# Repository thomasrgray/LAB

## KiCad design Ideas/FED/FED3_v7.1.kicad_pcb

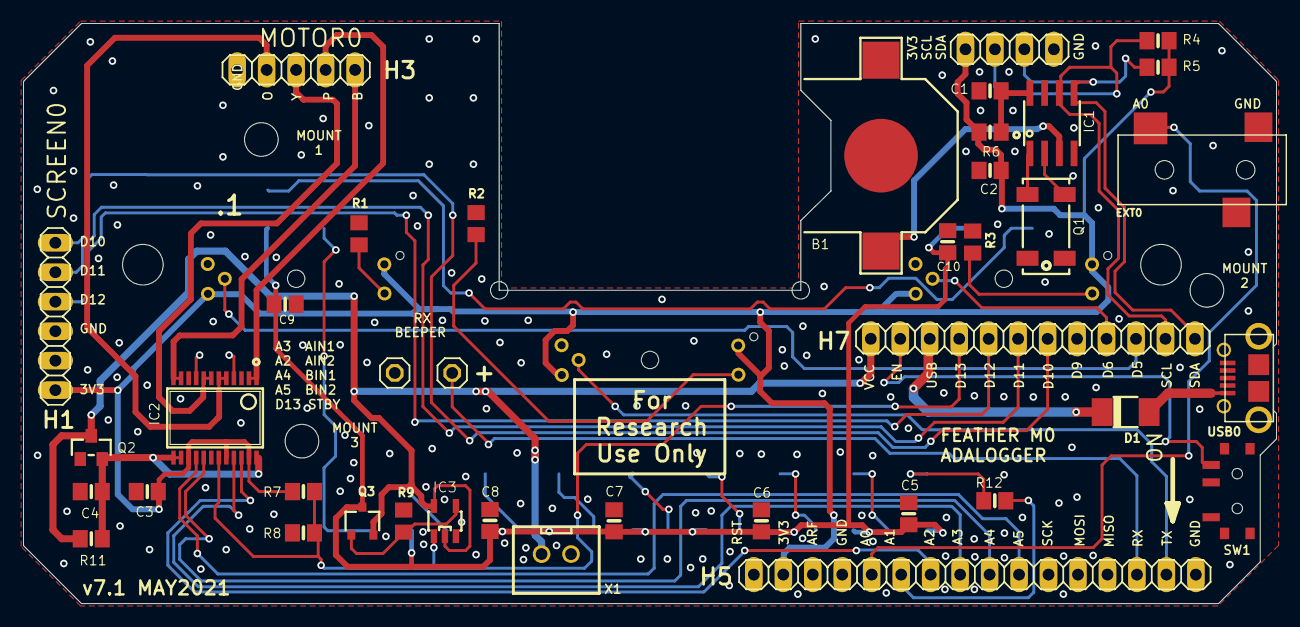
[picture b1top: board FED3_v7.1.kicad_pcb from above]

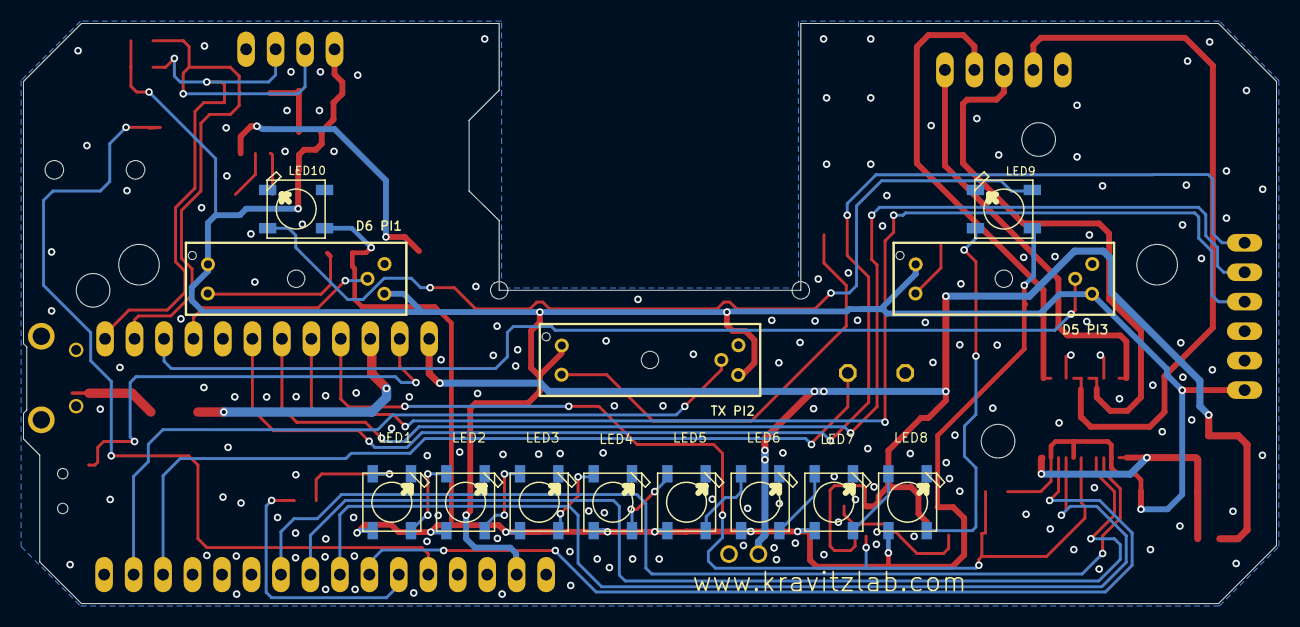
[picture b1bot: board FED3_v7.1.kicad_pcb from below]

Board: 2 copper layers, 108.0 x 50.0 mm, 60 parts (13 on the bottom side), 46 nets.

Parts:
@HOLE0, @HOLE1, @HOLE2, @HOLE3, @HOLE4, @HOLE5, @HOLE6: (no value)
AUX_I2C0: 1X04
B1: CR1220
BEEP1, BEEP2: 1X01
C1, C2, C5, C6, C7, C8, C9, C10: 10uF; 0805-NO
C3, C4: 10µF; 0805-NO
D1: DO-214AC
EXT0: 35RASMT2BHNTRX
FEATHER_L0: 1X16
FEATHER_R0: 1X12
IC1: RTC_PCF8523T; SOIC8_150MIL
IC2: TB6612 SSOP; SSOP24
IC3: M74VHC1GT50DTT1G; SOT23-5
LED1, LED2, LED3, LED4, LED5, LED6, LED7, LED8, LED9, LED10: WS2812B5050; WS2812B
MOTOR0: 1X05
PI1, PI2, PI3: GP1A57HR
Q1: 32.768; CRYSTAL_8X3.8
Q2: DMG3415; SOT23-WIDE
Q3: TSMT3
R1, R2, R3: 1k; R0805
R4, R5: 4K7; 0805-NO
R6: 1K; 0805-NO
R7: DNI; 0805-NO
R8: 4k7; 0805-NO
R9: 37k; R0805
R11: 0; 0805-NO
R12: 470; 0805-NO
SCREEN0: 1X06
SW1: SSSS811101
USB0: USB_MICRO_B; ZX62D-B-5P8
X1: B2B-PH-K-S(LF)(SN); JST-XH-02-PACKAGE-ROUND-PAD

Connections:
3V3: AUX_I2C0.1, C2.1, C3.1, FEATHER_L0.2, IC2.15, IC2.20, IC2.23, PI1.1, PI1.3, PI2.1, PI2.3, PI3.1, PI3.3, R4.1, R5.2, R6.1, R7.2, SCREEN0.6
A0: EXT0.4, FEATHER_L0.5
A1: FEATHER_L0.6, R12.2
A2: FEATHER_L0.7, IC2.22
A3: FEATHER_L0.8, IC2.21
A4: FEATHER_L0.9, IC2.17
A5: FEATHER_L0.10, IC2.16
BLUE: IC2.11, IC2.12, MOTOR0.5
D5: FEATHER_R0.10, PI3.4
D6: FEATHER_R0.9, PI1.4
D10: FEATHER_R0.7, SCREEN0.1
D11: FEATHER_R0.6, SCREEN0.2
D12: FEATHER_R0.5, SCREEN0.3
D13: FEATHER_R0.4, IC2.19, IC3.1, R7.1, R8.2
EN: FEATHER_R0.2, SW1.3
GND: AUX_I2C0.4, B1.-, BEEP2.1, C1.2, C2.2, C3.2, C4.2, C5.2, C6.2, C7.2, C8.2, C9.2, C10.2, EXT0.5, FEATHER_L0.4, FEATHER_L0.16, IC1.4, IC2.3, IC2.4, IC2.9, IC2.10, IC2.18, IC3.3, LED1.3-GND, LED2.3-GND, LED3.3-GND, LED4.3-GND, LED5.3-GND, LED6.3-GND, LED7.3-GND, LED8.3-GND, LED9.3-GND, LED10.3-GND, MOTOR0.1, PI1.5, PI2.5, PI3.5, Q2.1, R1.2, R2.2, R3.2, R8.1, R9.1, SCREEN0.4, SW1.2, USB0.P$5, X1.1
unnamed: PI2.2, R2.1
unnamed: PI3.2, R1.1
unnamed: PI1.2, R3.1
unnamed: D1.A, USB0.P$1
unnamed: LED1.2-DOUT, LED2.4-DIN
unnamed: C1.1, IC1.8, R6.2
unnamed: LED2.2-DOUT, LED3.4-DIN
unnamed: LED3.2-DOUT, LED4.4-DIN
unnamed: LED4.2-DOUT, LED5.4-DIN
unnamed: LED5.2-DOUT, LED6.4-DIN
unnamed: LED6.2-DOUT, LED7.4-DIN
unnamed: LED7.2-DOUT, LED8.4-DIN
unnamed: IC1.1, Q1.P$1
unnamed: IC1.2, Q1.P$4
unnamed: LED1.4-DIN, R12.1
unnamed: LED9.2-DOUT, LED10.4-DIN
unnamed: LED8.2-DOUT, LED9.4-DIN
ORANGE: IC2.5, IC2.6, MOTOR0.2
OUT3: IC3.4, Q3.P$1, R9.2
PINK: IC2.1, IC2.2, MOTOR0.4
RX: BEEP1.1, FEATHER_L0.14
SCL: AUX_I2C0.2, FEATHER_R0.11, IC1.6, R4.2
SDA: AUX_I2C0.3, FEATHER_R0.12, IC1.5, R5.1
TX: FEATHER_L0.15, PI2.4
USB: D1.C, FEATHER_R0.3
VBAT1: B1.+$1, IC1.3
VCC: FEATHER_R0.1, IC3.2, IC3.5, Q2.3, Q3.P$2, R11.2, X1.2
VCCNEO: C5.1, C6.1, C7.1, C8.1, C9.1, C10.1, LED1.1-VDD, LED2.1-VDD, LED3.1-VDD, LED4.1-VDD, LED5.1-VDD, LED6.1-VDD, LED7.1-VDD, LED8.1-VDD, LED9.1-VDD, LED10.1-VDD, Q3.P$3
VMOTOR: C4.1, IC2.13, IC2.14, IC2.24, Q2.2, R11.1
YELLOW: IC2.7, IC2.8, MOTOR0.3

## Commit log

2024-11-22 backup
2024-11-22 test
